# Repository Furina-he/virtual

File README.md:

# 电工电子技术虚拟仿真实训

基于 Electron、React、Three.js/react-three-fiber 与 ngspice 的离线电工电子虚拟实训桌面应用。

## 开发环境

- Node.js >= 22.12
- pnpm 10.12.3
- Windows 10/11 x64

```powershell
pnpm install
pnpm dev
```

## 验证命令

```powershell
pnpm test
pnpm e2e
pnpm typecheck
pnpm lint
pnpm content:lint
pnpm assets:lint
```

`pnpm e2e` 会先构建应用，再通过 Playwright 启动 Electron。`pnpm test` 包含真实 ngspice 金标准测试。

## 当前状态

- T0.9 接线编辑已完成。
- T0.10 首批资产管线与 19 个 GLB 已完成。
- T0.11 直流仪表与万用表的功能开发已完成，正式教学项目与目标机性能验收仍有遗留。
- T0.8 的 GTX 1650 级/核显目标机性能与冷启动验收尚未关闭。

当前 DG-01 是复用现有挂箱的仪表功能验证场景，不代表正式 `mod-dc-components` 教学内容已经交付。详细进度见 [执行计划](docs/03-执行计划.md) 和 [技术设计](docs/02-技术设计.md)。

## 目录

```text
content/    数据驱动的模块、仪表、项目与 SPICE 模型
src/        Electron 主进程、preload、renderer、仿真和纯 TypeScript 领域逻辑
resources/  ngspice、HDRI 等离线运行时资源
tests/      单元、金标准与 Electron E2E 测试
tools/      内容校验和 3D 资产生成/校验工具
docs/       PRD 配套技术文档与执行计划
```

## 第三方资源

运行时资产和第三方库的许可证记录见：

- [assets/LICENSES.csv](assets/LICENSES.csv)
- [content/ASSET-NOTICES.md](content/ASSET-NOTICES.md)
- [resources/ngspice/LICENSE-NOTES.md](resources/ngspice/LICENSE-NOTES.md)

内部厂商参考图片保存在本地 `assets/reference/`，默认不纳入公开仓库。仓库本身不附开源许可证；第三方组件和资产仍分别受其许可证约束。

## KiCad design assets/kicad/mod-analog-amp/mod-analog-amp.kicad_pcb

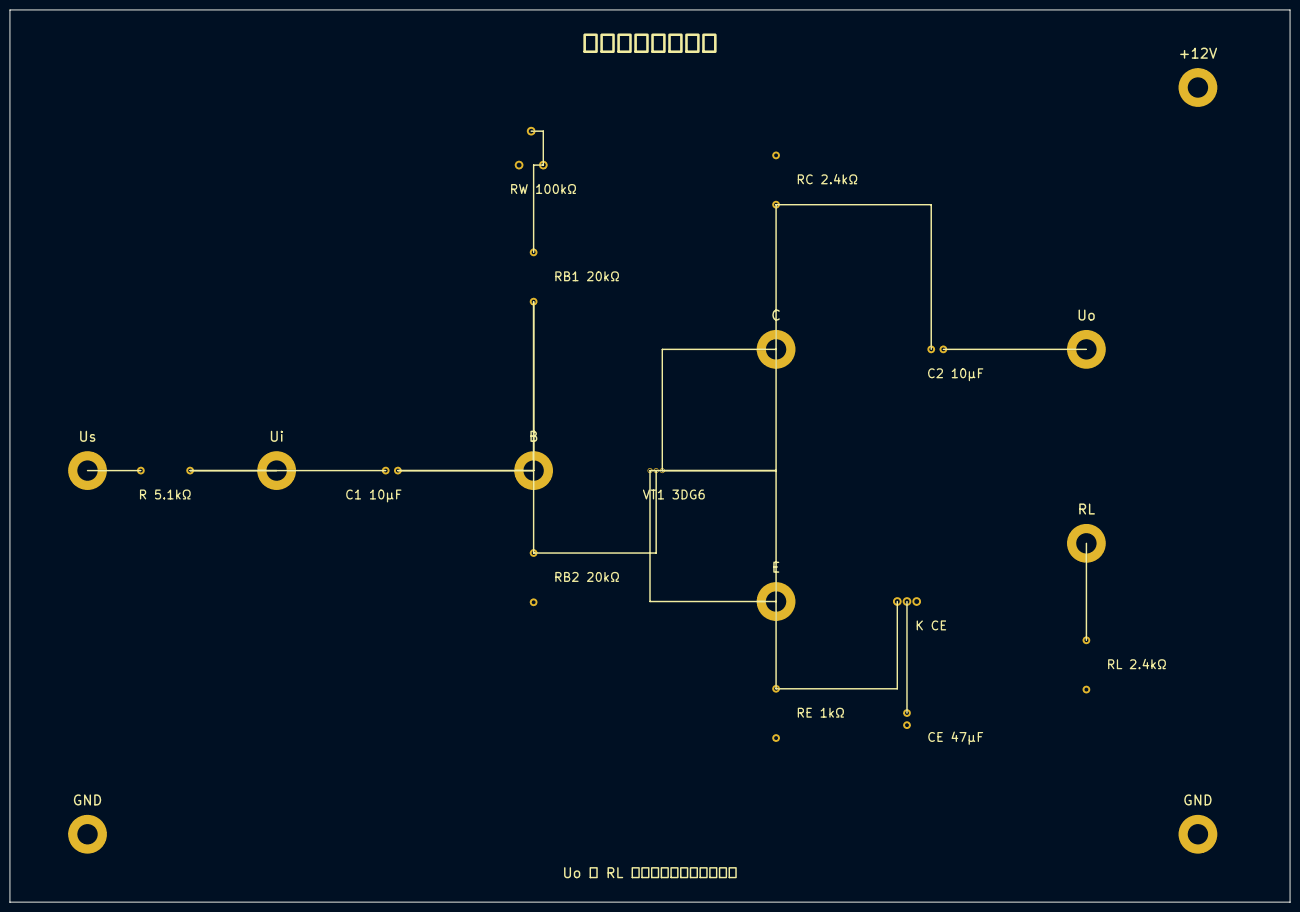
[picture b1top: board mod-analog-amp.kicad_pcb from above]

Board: 2 copper layers, 264.0 x 184.0 mm, 22 parts (0 on the bottom side), 11 nets, no tracks yet.

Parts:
C1, C2: 10μF; CP_Radial_D5.0mm_P2.50mm
CE: 47μF; CP_Radial_D5.0mm_P2.50mm
JACK_AMP_GND1, JACK_AMP_GND2: GND; Banana_Cliff_FCR7350B_S16N-PC_Horizontal
JACK_AMP_RL: RL; Banana_Cliff_FCR7350Y_S16N-PC_Horizontal
JACK_AMP_UB: B; Banana_Cliff_FCR7350Y_S16N-PC_Horizontal
JACK_AMP_UC: C; Banana_Cliff_FCR7350Y_S16N-PC_Horizontal
JACK_AMP_UE: E; Banana_Cliff_FCR7350Y_S16N-PC_Horizontal
JACK_AMP_UI: Ui; Banana_Cliff_FCR7350Y_S16N-PC_Horizontal
JACK_AMP_UO: Uo; Banana_Cliff_FCR7350Y_S16N-PC_Horizontal
JACK_AMP_US: Us; Banana_Cliff_FCR7350Y_S16N-PC_Horizontal
JACK_AMP_VCC: +12V; Banana_Cliff_FCR7350R_S16N-PC_Horizontal
KCE: CE接入/断开; SW_CuK_OS102011MA1QN1_SPDT_Angled
R1: 5.1kΩ; R_Axial_DIN0207_L6.3mm_D2.5mm_P10.16mm_Horizontal
RB1, RB2: 20kΩ; R_Axial_DIN0207_L6.3mm_D2.5mm_P10.16mm_Horizontal
RC: 2.4kΩ; R_Axial_DIN0207_L6.3mm_D2.5mm_P10.16mm_Horizontal
RE: 1kΩ; R_Axial_DIN0207_L6.3mm_D2.5mm_P10.16mm_Horizontal
RL: 2.4kΩ; R_Axial_DIN0207_L6.3mm_D2.5mm_P10.16mm_Horizontal
RW: 100kΩ; Potentiometer_Alps_RK09K_Single_Vertical
VT1: 3DG6; TO-92_Inline

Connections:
B: C1.1, JACK_AMP_UB.1, RB1.2, RB2.1, VT1.2
C: C2.1, JACK_AMP_UC.1, RC.2, VT1.3
E: JACK_AMP_UE.1, KCE.1, RE.1, VT1.1
GND: CE.2, JACK_AMP_GND1.1, JACK_AMP_GND2.1, RB2.2, RE.2, RL.2
RLP: JACK_AMP_RL.1, RL.1
UI: C1.2, JACK_AMP_UI.1, R1.2
UO: C2.2, JACK_AMP_UO.1
US: JACK_AMP_US.1, R1.1
VCC: JACK_AMP_VCC.1, RC.1, RW.1
nCE: CE.1, KCE.2
nRW: RB1.1, RW.2, RW.3

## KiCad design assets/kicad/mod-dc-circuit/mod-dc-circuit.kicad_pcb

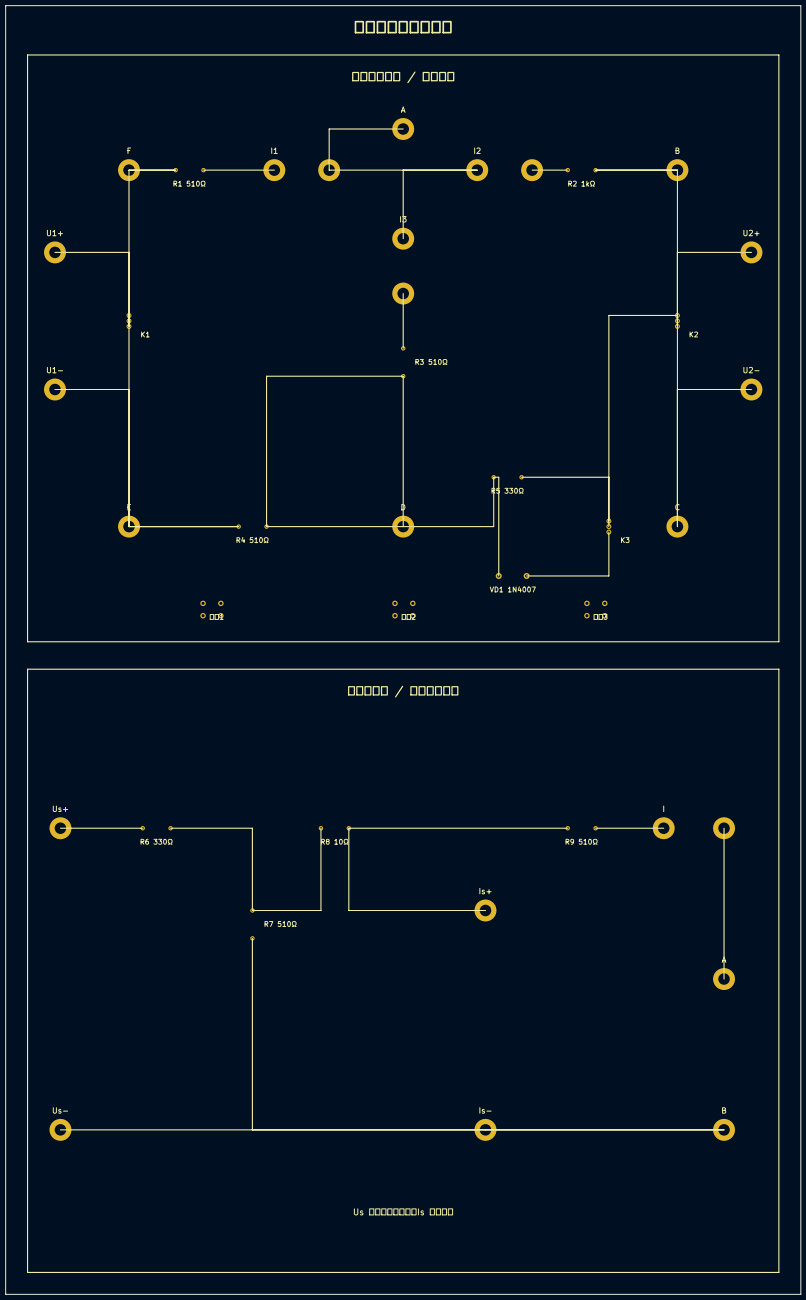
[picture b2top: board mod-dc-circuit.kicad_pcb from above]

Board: 2 copper layers, 290.0 x 470.0 mm, 40 parts (0 on the bottom side), 19 nets, no tracks yet.

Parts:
JACK_KH_A: A; Banana_Cliff_FCR7350Y_S16N-PC_Horizontal
JACK_KH_B: B; Banana_Cliff_FCR7350Y_S16N-PC_Horizontal
JACK_KH_C: C; Banana_Cliff_FCR7350Y_S16N-PC_Horizontal
JACK_KH_D: D; Banana_Cliff_FCR7350Y_S16N-PC_Horizontal
JACK_KH_E: E; Banana_Cliff_FCR7350Y_S16N-PC_Horizontal
JACK_KH_F: F; Banana_Cliff_FCR7350Y_S16N-PC_Horizontal
JACK_KH_I1A: I1; Banana_Cliff_FCR7350G_S16N-PC_Horizontal
JACK_KH_I1B: KH_I1B; Banana_Cliff_FCR7350G_S16N-PC_Horizontal
JACK_KH_I2A: I2; Banana_Cliff_FCR7350G_S16N-PC_Horizontal
JACK_KH_I2B: KH_I2B; Banana_Cliff_FCR7350G_S16N-PC_Horizontal
JACK_KH_I3A: I3; Banana_Cliff_FCR7350G_S16N-PC_Horizontal
JACK_KH_I3B: KH_I3B; Banana_Cliff_FCR7350G_S16N-PC_Horizontal
JACK_KH_U1N: U1-; Banana_Cliff_FCR7350B_S16N-PC_Horizontal
JACK_KH_U1P: U1+; Banana_Cliff_FCR7350R_S16N-PC_Horizontal
JACK_KH_U2N: U2-; Banana_Cliff_FCR7350B_S16N-PC_Horizontal
JACK_KH_U2P: U2+; Banana_Cliff_FCR7350R_S16N-PC_Horizontal
JACK_TH_A: A; Banana_Cliff_FCR7350Y_S16N-PC_Horizontal
JACK_TH_B: B; Banana_Cliff_FCR7350B_S16N-PC_Horizontal
JACK_TH_IA: I; Banana_Cliff_FCR7350G_S16N-PC_Horizontal
JACK_TH_IB: TH_IB; Banana_Cliff_FCR7350G_S16N-PC_Horizontal
JACK_TH_ISN: Is-; Banana_Cliff_FCR7350B_S16N-PC_Horizontal
JACK_TH_ISP: Is+; Banana_Cliff_FCR7350R_S16N-PC_Horizontal
JACK_TH_USN: Us-; Banana_Cliff_FCR7350B_S16N-PC_Horizontal
JACK_TH_USP: Us+; Banana_Cliff_FCR7350R_S16N-PC_Horizontal
K1: U1/短路; SW_CuK_OS102011MA1QN1_SPDT_Angled
K2: U2/短路; SW_CuK_OS102011MA1QN1_SPDT_Angled
K3: R5/VD1; SW_CuK_OS102011MA1QN1_SPDT_Angled
R1, R3, R4, R7, R9: 510Ω; R_Axial_DIN0207_L6.3mm_D2.5mm_P10.16mm_Horizontal
R2: 1kΩ; R_Axial_DIN0207_L6.3mm_D2.5mm_P10.16mm_Horizontal
R5, R6: 330Ω; R_Axial_DIN0207_L6.3mm_D2.5mm_P10.16mm_Horizontal
R8: 10Ω; R_Axial_DIN0207_L6.3mm_D2.5mm_P10.16mm_Horizontal
SB1: 故障1; SW_PUSH_6mm
SB2: 故障2; SW_PUSH_6mm
SB3: 故障3; SW_PUSH_6mm
VD1: 1N4007; D_DO-41_SOD81_P10.16mm_Horizontal

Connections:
A: JACK_KH_A.1, JACK_KH_I1B.1, JACK_KH_I2A.1, JACK_KH_I3A.1
B: JACK_KH_B.1, K2.2, R2.2
C: JACK_KH_C.1, JACK_KH_U2N.1, K2.3, K3.2
D: JACK_KH_D.1, R3.2, R4.2, R5.1, VD1.2
E: JACK_KH_E.1, JACK_KH_U1N.1, K1.3, R4.1
E1P: JACK_KH_U1P.1, K1.1
E2P: JACK_KH_U2P.1, K2.1
F: JACK_KH_F.1, K1.2, R1.1
TA: JACK_TH_A.1, JACK_TH_IB.1
TCOM: JACK_TH_B.1, JACK_TH_ISN.1, JACK_TH_USN.1, R7.2
TN1: R6.2, R7.1, R8.1
TN2: JACK_TH_ISP.1, R8.2, R9.1
TN3: JACK_TH_IA.1, R9.2
TUSP: JACK_TH_USP.1, R6.1
nAD: JACK_KH_I3B.1, R3.1
nBA: JACK_KH_I2B.1, R2.1
nDC1: K3.3, R5.2
nDC2: K3.1, VD1.1
nFA: JACK_KH_I1A.1, R1.2

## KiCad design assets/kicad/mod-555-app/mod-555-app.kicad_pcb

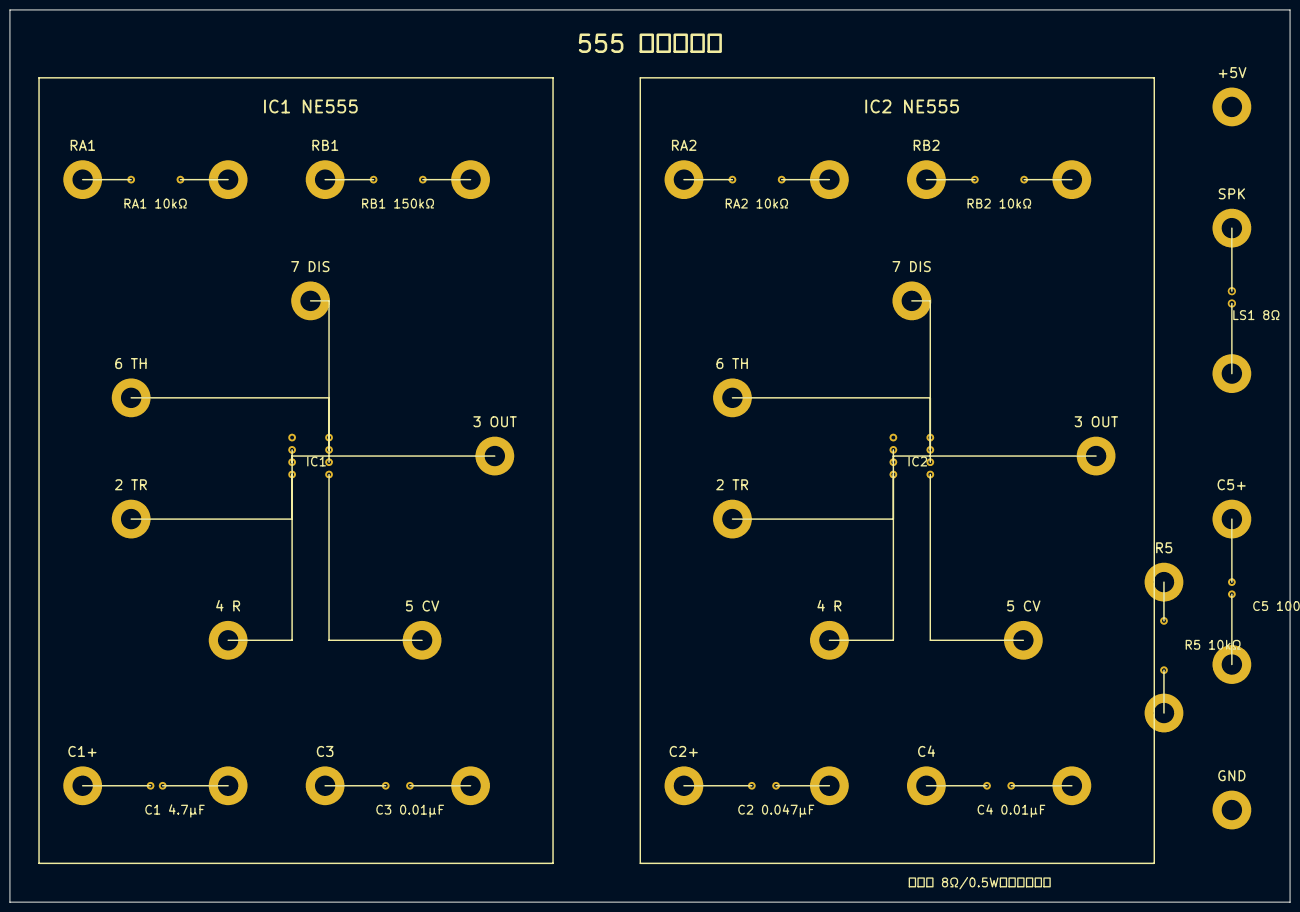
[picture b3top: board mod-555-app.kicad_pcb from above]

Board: 2 copper layers, 264.0 x 184.0 mm, 49 parts (0 on the bottom side), 36 nets, no tracks yet.

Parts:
C1: 4.7μF; CP_Radial_D5.0mm_P2.50mm
C2: 0.047μF; C_Disc_D5.0mm_W2.5mm_P5.00mm
C3, C4: 0.01μF; C_Disc_D5.0mm_W2.5mm_P5.00mm
C5: 100μF; CP_Radial_D5.0mm_P2.50mm
IC1, IC2: NE555; DIP-8_W7.62mm_Socket
JACK_C5_N: C5_N; Banana_Cliff_FCR7350Y_S16N-PC_Horizontal
JACK_C5_P: C5+; Banana_Cliff_FCR7350Y_S16N-PC_Horizontal
JACK_GND1: GND; Banana_Cliff_FCR7350B_S16N-PC_Horizontal
JACK_R5_1: R5; Banana_Cliff_FCR7350Y_S16N-PC_Horizontal
JACK_R5_2: R5_2; Banana_Cliff_FCR7350Y_S16N-PC_Horizontal
JACK_SPK_N: SPK_N; Banana_Cliff_FCR7350B_S16N-PC_Horizontal
JACK_SPK_P: SPK; Banana_Cliff_FCR7350Y_S16N-PC_Horizontal
JACK_T1_CC_1: C3; Banana_Cliff_FCR7350Y_S16N-PC_Horizontal
JACK_T1_CC_2: T1_CC_2; Banana_Cliff_FCR7350Y_S16N-PC_Horizontal
JACK_T1_CT_N: T1_CT_N; Banana_Cliff_FCR7350Y_S16N-PC_Horizontal
JACK_T1_CT_P: C1+; Banana_Cliff_FCR7350Y_S16N-PC_Horizontal
JACK_T1_CV, JACK_T2_CV: 5 CV; Banana_Cliff_FCR7350Y_S16N-PC_Horizontal
JACK_T1_DIS, JACK_T2_DIS: 7 DIS; Banana_Cliff_FCR7350Y_S16N-PC_Horizontal
JACK_T1_OUT, JACK_T2_OUT: 3 OUT; Banana_Cliff_FCR7350Y_S16N-PC_Horizontal
JACK_T1_RA_1: RA1; Banana_Cliff_FCR7350Y_S16N-PC_Horizontal
JACK_T1_RA_2: T1_RA_2; Banana_Cliff_FCR7350Y_S16N-PC_Horizontal
JACK_T1_RB_1: RB1; Banana_Cliff_FCR7350Y_S16N-PC_Horizontal
JACK_T1_RB_2: T1_RB_2; Banana_Cliff_FCR7350Y_S16N-PC_Horizontal
JACK_T1_RST, JACK_T2_RST: 4 R; Banana_Cliff_FCR7350Y_S16N-PC_Horizontal
JACK_T1_TH, JACK_T2_TH: 6 TH; Banana_Cliff_FCR7350Y_S16N-PC_Horizontal
JACK_T1_TR, JACK_T2_TR: 2 TR; Banana_Cliff_FCR7350Y_S16N-PC_Horizontal
JACK_T2_CC_1: C4; Banana_Cliff_FCR7350Y_S16N-PC_Horizontal
JACK_T2_CC_2: T2_CC_2; Banana_Cliff_FCR7350Y_S16N-PC_Horizontal
JACK_T2_CT_N: T2_CT_N; Banana_Cliff_FCR7350Y_S16N-PC_Horizontal
JACK_T2_CT_P: C2+; Banana_Cliff_FCR7350Y_S16N-PC_Horizontal
JACK_T2_RA_1: RA2; Banana_Cliff_FCR7350Y_S16N-PC_Horizontal
JACK_T2_RA_2: T2_RA_2; Banana_Cliff_FCR7350Y_S16N-PC_Horizontal
JACK_T2_RB_1: RB2; Banana_Cliff_FCR7350Y_S16N-PC_Horizontal
JACK_T2_RB_2: T2_RB_2; Banana_Cliff_FCR7350Y_S16N-PC_Horizontal
JACK_VCC1: +5V; Banana_Cliff_FCR7350R_S16N-PC_Horizontal
LS1: 8Ω 0.5W; PinHeader_1x02_P2.54mm_Vertical
R5: 10kΩ; R_Axial_DIN0207_L6.3mm_D2.5mm_P10.16mm_Horizontal
RA1, RA2: 10kΩ; R_Axial_DIN0207_L6.3mm_D2.5mm_P10.16mm_Horizontal
RB1: 150kΩ; R_Axial_DIN0207_L6.3mm_D2.5mm_P10.16mm_Horizontal
RB2: 10kΩ; R_Axial_DIN0207_L6.3mm_D2.5mm_P10.16mm_Horizontal

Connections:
GND: IC1.1, IC2.1, JACK_GND1.1
N1_CCa: C3.1, JACK_T1_CC_1.1
N1_CCb: C3.2, JACK_T1_CC_2.1
N1_CTn: C1.2, JACK_T1_CT_N.1
N1_CTp: C1.1, JACK_T1_CT_P.1
N1_CV: IC1.5, JACK_T1_CV.1
N1_DIS: IC1.7, JACK_T1_DIS.1
N1_OUT: IC1.3, JACK_T1_OUT.1
N1_RAa: JACK_T1_RA_1.1, RA1.1
N1_RAb: JACK_T1_RA_2.1, RA1.2
N1_RBa: JACK_T1_RB_1.1, RB1.1
N1_RBb: JACK_T1_RB_2.1, RB1.2
N1_RST: IC1.4, JACK_T1_RST.1
N1_TH: IC1.6, JACK_T1_TH.1
N1_TR: IC1.2, JACK_T1_TR.1
N2_CCa: C4.1, JACK_T2_CC_1.1
N2_CCb: C4.2, JACK_T2_CC_2.1
N2_CTn: C2.2, JACK_T2_CT_N.1
N2_CTp: C2.1, JACK_T2_CT_P.1
N2_CV: IC2.5, JACK_T2_CV.1
N2_DIS: IC2.7, JACK_T2_DIS.1
N2_OUT: IC2.3, JACK_T2_OUT.1
N2_RAa: JACK_T2_RA_1.1, RA2.1
N2_RAb: JACK_T2_RA_2.1, RA2.2
N2_RBa: JACK_T2_RB_1.1, RB2.1
N2_RBb: JACK_T2_RB_2.1, RB2.2
N2_RST: IC2.4, JACK_T2_RST.1
N2_TH: IC2.6, JACK_T2_TH.1
N2_TR: IC2.2, JACK_T2_TR.1
VCC: IC1.8, IC2.8, JACK_VCC1.1
nC5n: C5.2, JACK_C5_N.1
nC5p: C5.1, JACK_C5_P.1
nR5a: JACK_R5_1.1, R5.1
nR5b: JACK_R5_2.1, R5.2
nSPKn: JACK_SPK_N.1, LS1.2
nSPKp: JACK_SPK_P.1, LS1.1
